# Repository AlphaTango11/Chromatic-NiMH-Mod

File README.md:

# Chromatic Ni-MH Charging Mod

My first attempt to design, assemble, and integrate a real PCB from scratch as someone with very little (no) EE background.

### Purpose

Enables USB-C charging of Ni-MH batteries for the ModRetro Chromatic in a safe, cheap, and easy mod that only requires a bit of soldering.

The first board uses a simple, constant-current BQ25172DSGR configured to charge 3 Ni-MH AA cells at 83 mA for a maximum of 22 hours.

A standard Ni-MH Eneloop AA typically has a capacity of ~1900 mAh. This charge configuration would result in ~1850 mAh.

### Limitations

The charger is ideally used with nearly empty cells. If the cells are just below the recharge threshold of ~1.3 V (approximately 90% SoC), then they will reach "full" within a few hours but continue receiving current.

I am unsure of Eneloop's ability to self-catalyze like older Ni-MH cells. 83 mA is around C/23, which should be very safe even in the worst case, but I do not know of the risks or effects on cell life.

There is an overvoltage cutoff (1.7 V per cell), but the cells never reach that with 83 mA of current. In my charge tests, the cells will peak at around 1.5 V.
    
Alkaline batteries are not detected by this charger - it may try to charge them when plugged in. 
**Do not use the USB-C port with alkaline batteries installed.**

The LED is not really visible from inside the case. I can make an even smaller board without it, or I can add solderable leads to enable running it closer to a visible location.

## Assembly Steps

1. Remove Chromatic motherboard ([iFixit guide steps 1-5](https://www.ifixit.com/Guide/MODRETRO+Chromatic+Disassembly/180018))

2. Choose installation location (recommended: vacant micro SD slot or on top of MCU)
    - Plan wire routing and pay attention to button membrane locations/silkscreens.
    - I tried both the micro SD slot and on top of the MCU, but the LED was not visible. The top of the MCU may let the LED shine through the IR blaster area with more modification.
        - Do not try to put it on top of the ESP32, it won't fit back in the case.
    - I put kapton tape on the LCD to prevent any risk of shorting.

3. Connect wires:
   - 5V from TP16
   - GND from any ground point - I used the ground of a nearby capacitor
   - Battery output to TP7/Pin 3 of battery connector

4. Verify LED operation with batteries and USB-C cable connected
    - If the batteries are less than 1.3V, you should get a steady green LED.
    - If you don't see an LED, it may be because your batteries are too full. Verify all cells are <1.3 V.
    - *If the batteries are connected* and the LED is FLASHING, there is some other fault.
        - The LED will flash with no batteries connected.

5. Secure board as needed (dot of superglue, tape, etc.)

6. Reassemble device

## Pictures

## Components
    
I honestly don't know much about choosing components, but these are what I used. You may be able to do better.

10mm x 10mm V1.0

[Digikey Link for All Components (3 boards worth)](https://www.digikey.com/short/9fqp0m98)

[OSH Park Board Link](https://oshpark.com/shared_projects/6lf2HPNr) 

<a href="https://oshpark.com/shared_projects/6lf2HPNr"></img></a>

| Quantity | Component | Description | URL |
| ------------- | ------------- | ------------- | ------------- |
| 1 | BQ25172DSGR | 0.8-A, ONE- TO SIX-CELL NIMH STA | [Link](https://www.digikey.com/en/products/detail/texas-instruments/BQ25172DSGR/16585660) |
| 2 | CL05A106MP6NUN8 | CAP CER 10UF 10V X5R 0402 - INPUT/OUTPUT | [Link](https://www.digikey.com/en/products/detail/samsung-electro-mechanics/CL05A106MP6NUN8/10478957) |
| 3 | ERJ-2RKF3601X | RES SMD 3.6K OHM 1% 1/10W 0402 - STAT, ISET, TMR | [Link](https://www.digikey.com/en/products/detail/panasonic-electronic-components/ERJ-2RKF3601X/1746202) |
| 1 | ERJ-2RKF2402X | RES SMD 24K OHM 1% 1/10W 0402 - VSET | [Link](https://www.digikey.com/en/products/detail/panasonic-electronic-components/ERJ-2RKF2402X/1746163) |
| 1 | ERJ-2RKF1002X | RES SMD 10K OHM 1% 1/10W 0402 - TS | [Link](https://www.digikey.com/en/products/detail/panasonic-electronic-components/ERJ-2RKF1002X/192073) |
| 1 | APHHS1005CGCK | LED GREEN CLEAR CHIP SMD | [Link](https://www.digikey.com/en/products/detail/kingbright/APHHS1005CGCK/1747499) |

<br>

I highly recommend reading the [datasheet](https://www.ti.com/lit/ds/symlink/bq25172.pdf) for the BQ25172DSGR to get a better understanding of its operation.

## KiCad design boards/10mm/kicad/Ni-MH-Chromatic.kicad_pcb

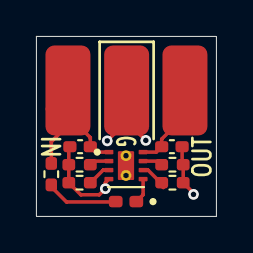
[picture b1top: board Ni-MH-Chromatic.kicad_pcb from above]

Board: 2 copper layers, 10.0 x 10.0 mm, 12 parts (0 on the bottom side), 9 nets.

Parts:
C1, C2: 10µF; C_0402_1005Metric_Pad0.74x0.62mm_HandSolder
D1: LED; LED_0402_1005Metric_Pad0.77x0.64mm_HandSolder
R1, R4, R5: 3.6K; R_0402_1005Metric_Pad0.72x0.64mm_HandSolder
R2: 24K; R_0402_1005Metric_Pad0.72x0.64mm_HandSolder
R3: 10K; R_0402_1005Metric_Pad0.72x0.64mm_HandSolder
TP1, TP2, TP3: TestPoint; Custom_TestPoint_Pad_2.5x5.0mm
U1: BQ25172DSGR; IC_BQ25172DSGR

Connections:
+5V: C1.1, R1.2, TP1.1, U1.1 (IN)
+BATT: C2.1, TP3.1, U1.8 (OUT)
GND: C1.2, C2.2, R2.2, R3.1, R4.1, R5.1, TP2.1, U1.4 (GND), U1.9 (EXP), U1.10 (GND/THERMAL), U1.11 (GND/THERMAL)
unnamed: D1.2 (A), R1.1
unnamed: D1.1 (K), U1.5 (STAT)
unnamed: R5.2, U1.2 (ISET)
unnamed: R4.2, U1.6 (TMR)
unnamed: R3.2, U1.3 (TS)
unnamed: R2.1, U1.7 (VSET)

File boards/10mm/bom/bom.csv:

"Reference","Value","Datasheet","Footprint","Qty","Description"
"C1,C2","10µF","~","Capacitor_SMD:C_0402_1005Metric_Pad0.74x0.62mm_HandSolder","2","Unpolarized capacitor - 1 - 10 uF"
"D1","LED","~","LED_SMD:LED_0402_1005Metric_Pad0.77x0.64mm_HandSolder","1","Light emitting diode - 5mA max draw"
"R1,R4,R5","3.6K","~","Resistor_SMD:R_0402_1005Metric_Pad0.72x0.64mm_HandSolder","3","Resistor"
"R2","24K","~","Resistor_SMD:R_0402_1005Metric_Pad0.72x0.64mm_HandSolder","1","Resistor"
"R3","10K","~","Resistor_SMD:R_0402_1005Metric_Pad0.72x0.64mm_HandSolder","1","Resistor"
"U1","BQ25172DSGR","","BQ25172DSGR:IC_BQ25172DSGR","1","Charging IC"

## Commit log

2025-01-03 Add BQ25172 Datasheet
